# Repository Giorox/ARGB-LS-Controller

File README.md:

# ARGB-LS-Controller
Circuit diagram, PCB layout and code for an ATTiny85 powered, addressable RGB LED strip controller.

# Repository organization

The circuit and board were developed using AutoDesk EAGLE and all files are available in the "Hardware files" folder. Schematic and Board layout PDFs can be found in the "Resources" folder. Controller code can be found in the "Code" folder.

# Project Requirements and Design

The PCB was developed to control any addressable RGB LED strip that uses WS2812B or similar LEDs that take 3 inputs (VCC, GND and Data/DIN) using any DIP8 packaged microcontroller.

All board traces are spec'd to handle up to 5A of current for PCBs fabricated at 1.6mm thickness and 1oz/mm2 allowing for LED strips of up to 88 LED long strips.

Circuit is current-protected up to 6A through a glass fuse at power input and power signal is conditioned using both input capacitors.

R1 is a pull-down resistor for the momentary SW2 push-button that allows for additional inputs to the microcontroller.

The board was developed to handle led-strip control through an ATTiny85 in the DIP8 packaging but should be compatible with all ATTiny microcontrollers in the same outer packaging.

All components are through-hole to reduce cost and facilitate construction.

# Bill of Materials

Besides the board and the led strip:

- 10K ohm resistor (Count: 1)
- 47uF electrolytic capacitor (Count: 1)
- 100nF ceramic capacitor (Count: 1)
- ATTiny85-20PU in DIP8 (Count: 1)
- 6A strand-glass fuse and support (Count: 1)
- Normally-open 4 terminal momentary push-button (Count: 1)
- 5.5mm barrel jack socket (Count: 1)
- SPST switch - Optional (Count: 1)
- DIP8 socket - Optional (Count: 1)

# Quirks

Version 1.0.0 of the board layout/schematic has improper pitch width for the 3 vias used for signal output to the led strip to be used as terminal bars. Pitch between terminals of the fuse are also non-standard, might require customization.

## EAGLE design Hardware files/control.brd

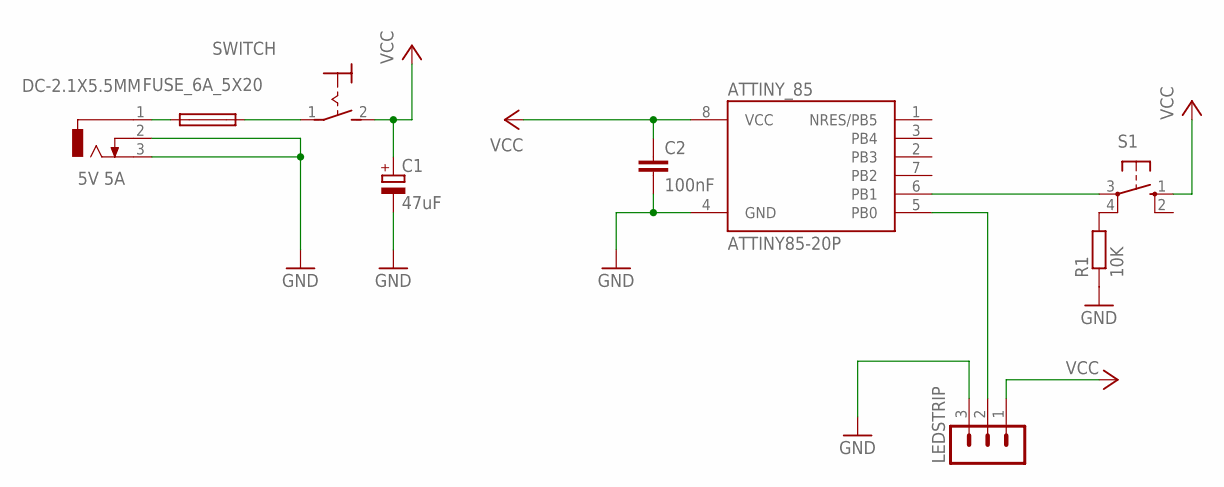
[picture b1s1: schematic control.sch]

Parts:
ATTINY_85: ATTINY85-20P; PDIP08_300MIL
C1: 47uF; E3,5-10
C2: 100nF; C025-025X050
DC-2.1X5.5MM: 5V 5A; DCJ0303
FUSE_6A_5X20: FUSEBLANK_5X20MM; FUSE_HOLDER_5X20MM
LEDSTRIP: MA03-1
R1: 10K; 0207/10
S1: 10-XX; B3F-10XX
SWITCH: MS243

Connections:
DATAIN: ATTINY_85.5 (PB0), LEDSTRIP.2
GND: ATTINY_85.4 (GND), C1.-, C2.2, DC-2.1X5.5MM.2, DC-2.1X5.5MM.3, LEDSTRIP.3, R1.1
unnamed: R1.2, S1.4 (P1)
unnamed: DC-2.1X5.5MM.1, FUSE_6A_5X20.1
unnamed: FUSE_6A_5X20.2, SWITCH.1
SWITCHIN: ATTINY_85.6 (PB1), S1.3
VCC: ATTINY_85.8 (VCC), C1.+, C2.1, LEDSTRIP.1, S1.1 (S), SWITCH.2 (S)

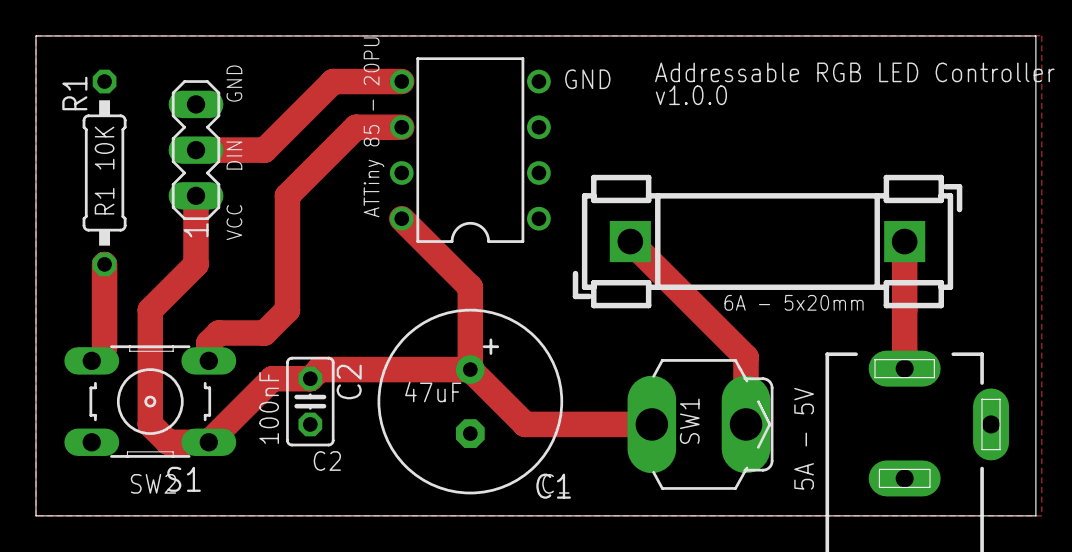
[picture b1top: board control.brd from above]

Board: 2 copper layers, 55.5 x 26.7 mm, 9 parts (0 on the bottom side), 7 nets.

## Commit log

2023-10-11 Initial upload
